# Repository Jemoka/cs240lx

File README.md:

## CS240lx Spr'26 (Y2E2-111 530pm)

This is a implementation-heavy, lab-based class.  We assume 140e as
a baseline and use this knowledge as a springboard to advance quickly
through a set of powerful, useful techniques that even many advanced
practioners don't know.

Like 140e you'll write custom code from scratch for the widely-used,
ARM-based raspberry pi; our code will run "bare-metal" without an
operating system, which means we can do interesting things without
constantly fighting with a lumbering OS that cannot get out of its
own way.

The course workload is significant, but we aim to not waste your
time. CS140E is strongly encouraged as a prerequisite, but a sufficiently
talented and motivated implementor can make up for its lack (as
calibration we usually have two or three people per year do this route).

### 240lx vs 140e 

Same rough format: 
  - still 2 days a week.
  - still hardware, low level code.
  - still pizza.

Contents:
  - Various cool tricks from 3+ decades of low level code.
  - Devices, speed, dynamic tools, code generation, OS tricks.  
    - Depends alot on what people are interested in.  
  - Probably at least one new board (pico, different riscv).

Differences:
  - usually stop around 10:30pm or so, vs 1:00am.
  - is more conceptual:
      - 140e must cover threads, interrupts, VM, FS, some network.
      - 240lx assumes you know that stuff, and use it to do
        other stuff.
  - class can replace cs240 (paper reading).
  - usually has the people who find 140e fun (+/-).
  - the final projects are wild.

Older versions:
  - [cs240lx-22](https://github.com/dddrrreee/cs240lx-22spr/tree/main/labs)
  - [cs240lx-23](https://github.com/dddrrreee/cs240lx-23spr/tree/main/labs)
  - [cs240lx-25](https://github.com/dddrrreee/cs240lx-25spr/tree/main/labs)

Alot of your favorite staff!
  - Head TA: Joseph Shetaye (rockets, booms, winning bets)
  - Maximilien Cura (Rust + insane hacks)
  - Aditya Sriram (ox64 riscv + bass)
  - Dawson Engler (sup)

---------------------------------------------------------------
### Class rules: no llm usage, no late labs.

This class is a brutal staff load.  140E last quarter:
 - Almost 2,000 checkoffs; 
 - Many (unpaid!) staff staying at lab from 530-midnight;
 - Everyone still has PTSD.

240lx has conceptually harder labs than 140e, much smaller staff, and
almost 2x last years enrollment.

So unfortunately we do have two draconian rules for survival.

*Rule 1: absolutely no labs accepted*:
  - You have 1 week to turn in each lab (earlier is better!).
  - We will not accept them after this.  
  - TAs can't deal with the load of late turn-ins.
  - Possible exceptions: you are presenting at a conference, 
    competing at a national championship, or doing a huge
    interesting extension.

*Rule 2: Absolutely no LLM usage for labs or extensions*:
  - You might not get caught, but if you do so we'll try to get you
    kicked out if you don't drop the class.
  - After the past year's experience, we've been forced into fascism.
  - The alternative is in-class blue book exams.  No one wants that.
  - If you want to use robots, *please* take the many other classes that
    are ok with it.  
  - There are much higher fidelity and much easier ways for us to see LLM
    output compared to the work and expense of this class.
  - WTS: we are developing "LLMs for low-level hardware" lab classes.  But
    they are intended as follow-on for those that understand how things
    work.

Sorry for the negative message. We live in interesting times. The path
ahead is unclear other than the neon glare of what has not worked well.

-----------------------------------------------------------------

### Possible labs

Always do: Generate executable code at runtime
  - even more low level than inline assembly.
  - self-modifying code is the ultimate sleazy hack.
  - used to make fast(er) interpreted languages (JIT for
    javascript, etc), fast dynamic intstrumentation (valgrind),
    and old school virtual machines (vmware).
  - can do all sorts of speed hacks by specializing using runtime
    information.  compiling data structures to code.  etc.

Always do: Custom pcb:
  - parthiv historically comes in to do a week of custom pcb labs so
    can make your own cool boards.

Always do: Build a bunch of tools using memory faults and single-stepping.
  - Eraser race detector 
  - Purify memory checker 
  - Advanced interleave checker.  
  - instruction level profiler measuring cycles, cache misses,
    etc.

Always do: Speed:
  - make low level operations (exceptions, fork/wait, pipe
    ping pong) 10-100x faster than laptop.  i think this is
    feasible but haven't done, so am interested.
  - overclocking the pi and seeing how fast can push it.
  - push the NRF using interrupts and concurrent tx, rx to 
    see how close can get to the hw limit.
  - make a digital analyzer (printk for electricity) where
    you get the error rate down to a small number of nanoseconds

And a few different communication protocols: 
  - how fast can send/recv data over gpio pins b/n two pis?
  - over IR
  - over speaker/mic.
  - over light and camera (?)
  - lora?

Device labs are fun.  So we do those too:
  - accelerometer, gyro
  - lidar
  - addressable light array
  - analog to digital converter.
  - lora so can send bytes 1km+

More systems-y device labs, by combining into
standalone tools:
  - acoustically reactive light display using mic, adc, 
    addressable light array.  extend to multiple systems.
  - little oscilliscope using oled display, mic, adc.

If we have more kernel hackers some subset of:
  - network bootloader
  - make an actual OS that ties all the stuff together.
  - small distributed system
  - distributed file system
  - actual clean fat32 r/w so can do distributed file system,
    firmware updates.
  - processes that migrate from one pi to another.
  - FUSE file system interface.

Big stuff missing from 140e:
  - makefiles
  - crazy C macro tricks.

Maybe other boards:
  - pico 2?  (slow, but small+cheap: has arm-m33 and risv)
  - ox64?  (risv)
  - if we do riscv: can write a simulator that will simulate itself
    on riscv in a couple of days.  can also make it symbolic.

Possible other stuf:
  - e.g., maybe some other languages (rust?  zig?)
  - static bug finder.

-----------------------------------------------------------------
### tl;dr:  getting setup.

  - get the class repo:

        git clone git@github.com:dddrrreee/cs240lx-26spr.git

  - define the `CS240LX_2026_PATH` environment variable to 
    point to where you put the class repo.  

        # for bash (in .bashrc or similar)
        export CS240LX_2026_PATH=<absolute path to your repo>

  - check that everything worked: plug in your pi, and run hello:

        % pwd
        /home/engler/class/cs240lx-26spr
        % cd labs/0-pi-setup
        % make

        ... alot of stuff ...
        listening on ttyusb=</dev/ttyUSB0>
        hello world from the pi
        DONE!!!
        
        Saw done

  - [look at the labs](./labs/README.md)
  - write code!

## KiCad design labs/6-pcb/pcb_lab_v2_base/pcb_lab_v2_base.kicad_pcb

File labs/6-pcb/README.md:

# PCB (KiCAD) Lab v2 by Parthiv

NOTE: KiCAD 10 was released last month (March 2026). I made this lab on KiCAD 9, but feel free to try KiCAD 10 and let me know if anything major has changed.

## Overview
This lab will be focused on designing printed circuit boards (PCBs), which many students in 140e/240lx/340lx have found useful over the years in final projects to help reduce wiring complexity and increase hardware reliability. The focus of the lab will be on how to replace a bundle of wires with an inexpensive PCB, and not on how to actually design electrical circuits (which is a much more complicated discussion). For the most part, you can get by just connecting breakout boards together. If you want to integrate a piece of hardware without a breakout board, most datasheets will include an "application circuit" that will show you what supporting hardware is needed.

Our goal is to create a board that can plug into the Raspberry Pi GPIO header and connect to a USB to UART converter along with some RGB LEDs. To extend the lab, you'll also add in connections to a few sensors/peripherals/hardware of your choice. 

## General Keyboard Shortcuts
I assume `Ctrl` becomes `Cmd` on mac.

* `Ctrl+S`: Save (do often!)
* `Ctrl+Z`: Undo
* `Ctrl+Y`: Redo

## Step 0: Prelab

Please review [PRELAB.md](./PRELAB.md). If interested, you can also check out a previous version of the lab [here](https://github.com/dddrrreee/cs240lx-23spr/tree/main/labs/16-pcb). In the original version of the lab, we focused on designing a board with NRF24L01 wireless transceivers. You can use that board for inspiration if you'd prefer to do something a little more "batteries included".

**A mouse will be very helpful!**

## Step 1: Creating a Project

1. Open up KiCAD (either type `kicad` in your terminal or search for it in your installed applications).
2. Go to File->New Project. Select a location where you want to create the project (you can do it in this directory) and give it a name. Ensure that the box to "Create a new folder for the project" is selected. Create the project.
3. You should see a window like this:

    On the left side, you can see a file called [project_name].kicad_pcb and another file called [project_name].kicad_sch. Double clicking these will open the PCB and Schematic editors respectively. We will learn what these are in more detail.

## Step 2: Creating a Schematic

1. In the main KiCAD window, double click the .kicad_sch file to open the Schematic editor. You'll probably get a popup saying that KiCAD is being run for the first time; just use the default option to "Copy default global symbol library table". Once that's done, you will see a blank schematic:

    The schematic is where we will describe what pins of what components connect to what other pins of other components. The analog here is your `.h` file. You'll definine the connections between components (like function interfaces) but not the actual physical implementation of those connections (like the function implementations in `.c`). You should try to keep this organized if you can! I will show you some strategies on how to do this. 

    You can middle click and drag to move, or scroll up/down to zoom. Ctrl+scroll will move you left/right and shift+scroll will move you up and down, if you prefer that to middle click and drag.

2. Go to Place->Add Symbol (or type the keyboard shortcut `A`). Again, if you get a popup here, "Copy default global footprint library". In the search bar, search for the symbol `Raspberry_Pi_2_3`. Select it, then click OK to start placing the component. Place it somewhere in the middle of the schematic by clicking. If you want to move it, you can click on it, hit `M`, and then move it around, then click again to place it. You'll immediately notice that the pins are laid out quite differently from the actual physical pins on the Pi. And you'll see just one GND, 5V, and 3.3V pin, though the Pi has many. This is one of the ways that we simplify the schematic view to make it a bit easier to see what's going on. In older versions of KiCAD, you may see all of the power pins represented; if so, you can just wire them all together in the schematic (see old version of the lab).

3. Now, we will connect the power rails of the Raspberry Pi. Hit `P` to open up the power symbol menu. Search for `GND`, select it, and hit OK to start placing the ground symbol. Put it near the bottom of the Raspberry Pi symbol. Hover over the end of one of the GND pins on the Pi, then hit `W` to start drawing a wire. Note that it'll start drawing a wire from wherever your mouse was; if it was in a bad spot, you can click `Esc` to cancel drawing the wire and try again. Connect the Pi's GND pin to the GND symbol you just placed.

    Next, add power symbols for `+5V` and `+3V3` to the schematic, and connect those to the 5V and 3V3 pins of the Pi.

4. Now that we've connected the power for the Pi, let's add the RGB LEDs. We are going to use the SK6812 LEDs, which are compatible with the more common WS2812 but work with the 3.3V logic level that the Pi outputs. Technically, WS2812 require 5V logic (though we often get away with 3.3V for small chains). You can review the SK6812 datasheet in [docs/SK6812.pdf](docs/SK6812.pdf). It's a pretty short datasheet and worth looking through the whole thing.

    In the schematic view, type `A` to add a new component, then search for `SK6812`. Place a few of them down (however many you'd like)! You can also just place one, click `Esc` to get out of the add component mode, then left click and drag to select the LED you placed, then Ctrl+C/Ctrl+V to duplicate it however many times. 
    
    Something to know is VDD (or sometimes VCC) in datasheets or component pinouts refers to the positive voltage, while VSS (or VEE) refers to ground.
    
    If you read the datasheet (read the datasheet!), you'll see that the manufacturer recommends placing capacitors between the 5V supply and ground near each of the LEDs. This is a pretty common thing you'll see to help provide a more stable voltage supply to more power-hungry components. Usually, they'll specify the capacitance properly (in pF, uF, or nF), but here you can see a 3-number code of `104`. A quick search will tell you that `104` is 100nF or 0.1uF. Let's add these capacitors too; the name in the parts menu is `C`.
    
    Go ahead and connect +5V and GND sources to each of the LEDs as required (type `P` to add power sources, `W` to draw wires). When drawing wires, if you click before reaching your destination, you'll get to decide where the wire turns in the schematic view which can be helpful for organization. It's common to just have a whole bunch of power sources all over the schematic to avoid drawing long wires between them. There is an implied connection between all sources with the same label. 

    Pro-tip: you can make one LED/capacitor/wires/sources unit and then copy/paste that a few times. 

    Apply the capacitance value to the capacitors by clicking on the capacitor, then typing `E` to edit. Then in the popup window, update the value in the `Value` field. This isn't enforced in any way, it's just a note so you know what it is when you're placing the capacitors on the PCB.

    Choose a Pi pin to connect the first LED's DIN port to. I chose GPIO12 (which is incidentally pin 32). Your schematic should look something like this:

5. Now, let's create a connector for a [USB/UART converter breakout board](https://www.amazon.com/MTDELE-CP2102-Serial-Adapter-Module/dp/B0D76NNWVW) so we can plug it directly into the PCB. Unfortunately, most breakout boards won't have an associated symbol in KiCAD, but it's good practice for creating new symbols. We'll want to create a symbol to represent the logical pins that the USB/UART has. Go to Tools->Symbol Editor. You will see a blank symbol editor like this:

    On the left, you can see various symbol libraries which contain different default parts that are common enough to be included in KiCAD. We will be creating a new one.

    In the symbol editor, go to File->New Library. If you make it Project, any parts you make will only be usable in the current project. If you make it Global, you can use it in future projects. I went with Project but either is ok. Give it whatever name you want (`cs340lx_pcb`, or something).

    On the left window, find the library you created and right click on it. Then click New Symbol, and you'll see a new window pop up. See below for recommended settings.

    Click on OK and create it. 

    ```
    If you can't find the library (seems to be happening on KiCAD 10), try the following workaround: 
    1. Go to `Preferences -> Manage Symbol Libraries` and then click `Project Specific Libraries`
    2. Delete the custom library if it's present.
    3. Re-add the library.
    ```

    On the left of the main window (to the right of the list of libraries), right click on the grid and select Edit Grids.

    In the window that shows up, change the Fast Grid Switching: Grid 1 to 100mil/2.54mm. This helps with alignment for placing pins in the symbol. Then close this window, and type `Alt+1` to switch to the 100mil/2.54mm grid. Make sure the bottom of the symbol editor shows `grid 100`.
    
    Now that setup is done, it's time to make the symbol. On the right side of the main window, select the Draw Rectangles tool and draw a rectangle on the screen. Don't worry, you can change it later. If you want to move the auto-generated text (`J`), you can click on it (press escape to reach select mode like in the schematic editor) and hit `M` to move it. Click to place.

    Now, we will add the pins. Hit `P` to create a pin. We'll make the `GND` pin, which is pin number 4 (4th from the top of the UART) and is a Power Output. The reason we choose Output is because the entire system's power/ground is going to be generated by the UART plugged into your computer.

    Place the pin down at the bottom of the rectangle, ensuring that the circle end of the pin is facing out (this is where you'll connect wires in the schematic). Click `R` to rotate the pin.

    Create the remaining 4 pins:

    - 1: 3V3, power output
    - 2: TX, output
    - 3: RX, input
    - 4: GND, power output (already did in step 11)
    - 5: 5V, power output

    Try to keep voltage at the top, ground at the bottom, and signals on the sides (like the Raspberry Pi symbol). You can grow and shrink the rectangle if needed by going to the select tool (escape) and then clicking on the border of the recctangle. Your symbol should look something like this (doesn't have to match exactly). You can rotate a pin with `R` and move with `M` like you'd expect.

    You can add text using the text tool on the right side. Once you've finished the UART symbol, save with Ctrl-S or Command-S, then exit the symbol editor. In the schematic editor, click `A` to add a symbol. Search for the UART you just created; you should see it pop up.

    Connect the 5V pin to your +5V rail, GND to GND, TX to the Pi RX and RX to the Pi TX. You can optionally connect 3V3 to +3V3, but this isn't strictly necessary since the Pi also creates its own 3V3 on the pins. I left it unconnected.

    By convention, if wires appear to cross but don't have a circle over the intersection, they are considered to NOT be connected.

    Hover over an unused pin on the Pi and hit `Q` to mark it as a No-Connect (looks like an X). This declares that you meant to not connect this pin and didn't just forget to connect it. Now, you're in no-connect placing mode and you can click on all the unused pins on the Pi/LEDs/UART/your custom hardware. Compare your schematic against the Completed Schematic section below, making sure that everything is connected the way it should be.

6. Create and add new symbols for your selected sensors of choice. If you used breakout boards, there should be very little/no additional supporting hardware and you should just be able to wire up to pins on the Pi. You can check datasheets or hookup guides to be sure. Feel free to ask Parthiv for help/confirmation. Make sure your pins are numbered correctly, which will make things much easier later on.

7. Annotate the schematic with `Tools->Annotate Schematic`. A window will pop up, click Annotate, which assigns reference designators (`C1`, `J2`, etc) to all the symbols. Click `Close`.

8. Now, go to `Inspect->Electrical Rules Checker` and click Run ERC to run the ERC. Make sure you annotate the schematic first; otherwise, you get a ton of weird errors. This is like a type checker in software; it will catch violations of electrical rules (type rules) but NOT correctness. And sometimes it rejects valid schematics (like a type checker can reject valid programs), which you will see.

    You will hopefully see 0-1 errors. If you connected the UART 3V3 to +3V3, you will not get the error I have. This error is because whoever made the Raspberry Pi Symbol decided to make the 3V3 pin a power input even though it's a power output. So the ERC thinks nobody is providing power to +3V3. We know this to be wrong (the Pi outputs 3V3) so we can ignore this.

    If you have other errors, address them and re-run ERC. A common error is forgetting to put a no-connect on a pin that is unconnected. Also, be careful with custom symbols that you properly assigned the pin types.

9. The last step is to assign footprints, which are the representation of each symbol in the real world PCB. Go to `Tools->Assign Footprints`, which will open a new window. 

    You will see that the LEDs have footprints already assigned. It's worthwhile to check the datasheet to make sure these are correct. We need to assign footprints for the other components. Click on the row with C1, then on the left side look for library `Capacitor_SMD` (capacitor, surface mount device). On the right side, look for footprint `Capacitor_SMD:C_0603_1608Metric`. This corresponds to a standard 0603 surface mount capacitor, which is a super common size. Double click on `Capacitor_SMD:C_0603_1608Metric`, which will assign that footprint to our capacitor.

    Go through and do this for all the components:

    - Both capacitors: `Capacitor_SMD:C_0603_1608Metric`
    - Pi: Library `Connector_PinSocket_2.54mm`, footprint `Connector_PinSocket_2.54mm:PinSocket_2x20_P2.54mm_Vertical` (0.1" female header, 2x20)
    - UART: Library `Connector_PinSocket_2.54mm`, footprint `Connector_PinSocket_2.54mm:PinSocket_1x05_P2.54mm_Horizontal` (0.1" female 90 degree header, 1x5).
    - Your selected breakout boards: probably a 2.54mm 1xN PinSocket for some N.

    Then click "Apply, Save Schematic & Continue". You can then close out of the Assign Footprints window and the schematic editor.

### Schematic Editor Keyboard Shortcuts

* `A`: add symbol
* `P`: add power symbol
* `Esc`: go to regular mouse (select) mode
* `M`: move (after selecting a symbol)
* `R`: rotate (after selecting a symbol)
* `E`: edit symbol properties (after selecting a symbol)
* `Q`: place no-connect symbol (should be in select mode first)
* `W`: draw wire (should be in select mode first)

### Schematic Editor Tools

* Tools->Symbol Editor: create new symbols
* Tools->Annotate Schematic: assign reference designators
* Tools->Assign Footprints: assign PCB footprints to schematic symbols
* Inspect->Electrical Rules Checker: validate against some rules

### Symbol Editor Keyboard Shortcuts

* `P`: add pin
* `Esc`: go to regular mouse (select) mode
* `M`: move (after selecting a symbol)
* `R`: rotate (after selecting a symbol)your Schematic 

## Step 2: Laying out the PCB

Time to create the PCB! For all of these steps, you don't have to match the exact thing I do. Actually better if you don't, so it's your board and not you making my board :D

1. From the KiCAD main window, double click the .kicad_pcb file to open the PCB editor. You will see a blank PCB, this time a black background instead of white (schematic).

    You can middle click and drag to move, or scroll up/down to zoom. Ctrl+scroll will move you left/right and shift+scroll will move you up and down, if you prefer that to middle click and drag.

2. Go to Tools->Update PCB From Schematic. This will open a window, click "Update PCB". You should do this any time you edit your schematic or assign new footprints in the schematic.

    Hopefully, there are zero warnings/errors. A common error is forgetting to assign a footprint to a symbol in the schematic. If you do this, then KiCAD is unsure what physical footprint to assign to the logical symbol you created in the schematic. Revisit step 19 from part 1 if this happens. Then, come back to the PCB viewer and this step again.

    If you have zero warnings/errors, then you can "Close" the window that popped up, and then click anywhere to place the mess of components.

    You will see a 2x20 pin header for the Pi, 1x5 header for the UART, LEDs, capacitors, and any additional headers/components for your chosen hardware.

    If you look at the picture at the very top of this page, you will see that the Pi header is on the underside of the board whereas everything else is on the top. To move the Pi connector to the backside of the board, click on it, then hit `F` to "flip" it to the back. You will see the outline change from pink to blue, and also the text related to the Pi header will be mirrored. 

    You can also go to View->3D viewer to see this, though there will probably be an error about not having a board outline yet (which we will fix shortly).

3. Now, we will try to organize the components reasonably well to minimize the length of the connections we need to make. Hit `Esc` to go to select mode, then click on any footprint. Once you've selected the footprint, you can rotate it with `R` or move it with `M`. Click to place when you're in move mode. 

    All of the thin lines you see connecting the different pins of components are connections we will eventually need to make, so trying to keep these as "untangled" as possible will make things easier. That being said, it's probably impossible to completely avoid crossing (it's not an issue to have crossing wires as we can route wires on the front and back of the board).

    I would recommend putting the Pi header at the top of the other components, with the +5V pads to the left. Then, put the UART near the left side of the Pi header (so there's a short path for +5V).

    Also, make sure to keep each capacitor close to the +5V pad of one of the LEDs. Technically, the way that our schematic is, we could connect them to anywhere on +5V and GND. However, we would like to keep the resistance on the path between the capacitor and the LED as small as possible, so that the capacitor can deliver power to the LED when it has current spikes when turned on bright. Here's one possible arrangement which is pretty reasonable:

    You'll see I assigned the wrong footprint for the UART (not a Horizontal/right angle header) so I went ahead and fixed that in the Schematic editor (Tools->Assign Footprints) then went back to the PCB editor and ran Tools->Update PCB from Schematic.

    If you're particular about alignment, you can select multiple components with Shift-Click and then right click. In the menu, select "Align/Distribute" and mess around till you get what you want. 

4. Now let's draw our board outlines. On the right side, you will see a bunch of Layers

    These each represent a different layer of the PCB. Some highlights:
    * `F` and `B` prefixes are for front and back, as we can have many things on either side of the board
    * `Cu`: front and back copper, which are where we make our connections. In a more-than-2 layer board, we will have `In1.Cu`, `In2.Cu`, etc.
    * `Adhesive`: some components are glued to the board, this layer shows where the glue should be placed
    * `Paste`: for surface-mount components, this is where the machine will automatically place solder paste. After components are automatically placed in their locations, the whole board is baked, melting the solder paste, then cooled, hardening the paste (and making electrical/mechanical connection with the components).
    * `Silkscreen`: text/drawings that are printed on the board for aesthetic/documentation reasons
    * `Mask`: The green (or other color) layer of the board which protects the underlying copper from corrosion and accidental shorts. It's expected that most of the board has mask, so the `Mask` layer is actually the negative. So it shows where there is _not_ mask.
    * `User.*`: these don't get printed, so you can put stuff for documentation
    * `Edge.Cuts`: the edges of the board which are cut.
    * `Courtyard`: bounding polygons for the various components. Ideally, no courtyards overlap so we can ensure that no components are inside each other. Just like we had an ERC in schematic, we have a DRC (design rules check) for the PCB which will complain if two courtyards overlap. However sometimes we know that we are safe (e.g. capacitor fits "under" NRF).

    You can enable/disable the visibility of layers by clicking the eye icon, which can be interesting. 

    You'll want to click on the `Edge.Cuts` layer and make sure the triangle is pointing to it (like in the image above). Select the rectangle tool (also selected in the image above). Now, draw a rectangle around the components you made by clicking once for one corner, then clicking again for the opposite corner. Give yourself some extra space for routing traces (wires) around the components. 

    Now, if you open View->3D Viewer, you will see your new outline.

    If you make it too big/too small, you can always edit this by clicking on the `Edge.Cuts` layer, then the select tool (`Esc`), then clicking on the corner of the rectangle and changing the shape. 

    You can also make a custom shape using a vector graphics tool like inkscape, then export as SVG. Then go to File->Import->Graphics and add your shape to the `Edge.Cuts` layer.

5. A common practice in PCB design is to make (almost) the entire front of the board be connected to your power rail, and (almost) the entire back of the board be connected to your ground rail (or vice versa). This helps you avoid having to manually connect every power and ground together, sort of like how we just connected them to the GND and +5V symbols on the schematic to avoid a ratsnest of wires between the power pins.

    We will do that now. Click on the `F.Cu` layer and do `Ctrl+Shift+Z` (mac: `Option+Z`) to open a window for "copper zone". Ensure that the `F.Cu` layer is selected on the left, then select the `+5V` net.

    Hit OK, then draw a rectangle that's bigger than the rectangle you drew for the edge cuts (this time, you need to click all 4 corners, not just 2 opposite). Repeat the process for `B.Cu` and `GND`. It should look something like this when you're done:

    If you mess up while you're drawing, you can hit `Esc` and try again.

6. Let's actually fill the zones to make the electrical connections. Hit `B` to fill zones. This should hopefully connect all of our +5V and GND connections for us! You'll see the connection lines for those disappear. If you zoom in to some pins, you will see what exactly happened:

    Notice that on the front side (red), where we made the 5V zone, KiCAD helpfully connected the pin with an X pattern. On the back side (blue), where we made the GND zone, KiCAD connected with an X pattern. It may be easier to see what's going on if you make one of the two copper layers invisible (see above). Make sure to turn it back on afterwards.

7. Now the fun begins: time to route our traces! Click on `F.Cu` on the left to route on the front of the board. Then, select a `1 mm` trace width. Move your mouse over the +5V pad on the UART (you can zoom with scroll wheel, and middle click+drag to pan). Hit `X` to enter trace mode. If you move your mouse, you will see a trace expanding out of the pad. 

    Each time you click in trace mode, you will "save" some of your progress that you've made. Once you reach your target, you can click on it to finish routing the trace. In general, try to avoid 90 degree turns. 

    Go ahead and connect the Pi pin you selected for the LED signal to the first LED. It's ok to go in between the pins of the Pi. Then, hit `B` to re-fill the zones, and you'll see a bit of the front +5V zone has been cleared out to allow the trace you just made to go through it. 

    Let's now route the other 2 UART connections. I started doing that, but it seems like my traces will have to cross!

    We have a few options on how to solve this. We can go all the way around with one of the connections.

    But you'll notice this cut off the Pi's +5V pins from the rest of the +5V zone, making an "island". KiCAD is drawing a short connection line between the main zone and the "island" to inform us of this. We could go ahead and connect this, but it's not ideal.

    We have two layers! We could, for example, just cross the signals by moving one to the back of the board. While routing one of the signals (with `X`), click `V` to enter Via mode, and then place the Via somewhere so you can swap sides of the board. Since the UART Module uses through-hole pins, it can connect directly on the backside to the backside trace. Surface mount components (like our LEDs and capacitors) can only connect on the side they're placed on, so you'd need another via to bring the signal back to the front.

    We can also just route the whole signal on the back of the board. If you're not currently routing any trace (`Esc`), then clicking `V` will swap you between the front and the back. If you're on the back, the board will appear blue. 

    This is a bit of a contrived/silly example, but hopefully it demonstrates that you have a lot of options available when routing more complicated netlists. You may have to experiment with different solutions to problems and backtrack if things get too complicated. An absolute worst case scenario is to go a 4-layer board. It just increases cost (though not by a lot if you are ok with all your vias going all the way through the board). Most projects you'd do should be routable on 2 layers.

8. Finish up routing the surface mount components. You'll notice that the GND pins on the LEDs and capacitors cannot connect to the GND plane on the back; this is because they are surface mount components and only connect to the front by default. Add vias for those, either by starting a routing with `X` and then hitting `V` to place a via, or by hitting `Ctrl+Shift+X` to place a via directly. After placing the via and selecting the GND net, you can then route.
    
    Finish up routing your custom hardware, then save (hopefully you've been doing this throughout). You can admire your work in the View->3D Viewer!

9. I would recommend adding some annotations on the Silkscreen. You can click the `F.Silkscreen` (or `B.Silkscreen`) on the right side, then the text tool, and add annotations. At the very least, it's good to write the pin names on the various connectors (or at least enough that you plug it in the right way). And label the different connectors if you have several.

    My completed base PCB:

10. Almost done with the board! Let's run DRC (design rules checker) which will make sure our board is manufacturable. Go to Inspect->Design Rules Checker. In the window that pops up, enable "Test for parity between PCB and schematic" just to be sure.

Click Run DRC. If you have errors, go to the DRC Errors section below for common errors. For each, I'd recommend you zoom in super close, then click the entry in the DRC window. You will see an arrow in the middle of your screen. Address the issue and then click Run DRC in the window again. If there are other errors, ask me and I can help you out. 

If you get an error about the two +3V3 pads not being connected, this is because we don't actually use those for anything. If you'd like, you can disconnect the +3V3 in your schematic, mark it not-connected, and then return to the PCB and Update PCB from Schematic. Then, the connection requirement should disappear and DRC will be clean.

### Routing Tips

#### Clearance
Try to give clearance to pads and don't route traces too close to them (especially ones that connect to planes). This makes it easier in the future to route signals from those pads.

#### Try, try, try again

Don't be afraid to delete an old trace and re-route it if you find you need to move it to make something else work.

#### Zone Islands
An extremely common issue that people ran into was creating a filled zone "island", like below: 

Notice how the two traces have created an almost closed-loop, which cuts off a section of the filled zone into an island that's disconnected from the rest. An easy fix is to open the closed loop by moving one or more of the segments of the traces onto the other layer. If you go to the select mode (`Esc`), then click on a piece of trace, then hit `E`, then swap the layer to the other layer. You can then go and place vias (`Ctrl+Shift+V`, or `Opt+V` for mac?) on each end of the segment that you flipped to the other side to make electrical connection.

Another (worse) solution is to to put a via on the island and off the island and route a "jump" on the other side of the board. This isn't really recommended though, since it means there is higher resistance on the power plane (vias introduce resistance).

### DRC Errors

Here are some common DRC errors/warnings

#### Track has unconnected end

You have some track that is only connected on one side and can just be deleted. A tricky one is when the track is contained entirely inside a pad hole, so it's invisible (see below). Just click on the exact tip of the arrow that is pointing out the error and it should get highlighted. Then just hit `Del`. It helps to be VERY zoomed in on the PCB editor window.

#### Silkscreen clipped by solder mask

You have silkscreen that is either drawn off the edge of the board, or overlaps a pad somehow. Either expand your board (go to `Edge.Cuts` layer, then `Esc` to select, then click and expand the rectangle). Or move the silkscreen item (go to appropriate `*.Silkscreen` layer, then `Esc` to select, then click item, then `M` to move it). Below you can see I drew my board too small so the silkscreen hangs off the edge.

### PCB Editor Keyboard Shortcuts
* `Esc`: go to regular mouse (select) mode
* `M`: move (after selecting a footprint)
* `R`: rotate (after selecting a footprint)
* `F`: flip footprint (after selecting a footprint)
* `Ctrl+Shift+Z` (or `Opt+Z` on Mac?): create filled zone
* `B`: fill zones
* `X`: route trace
* `V`: swap active copper layer (front to back or vice versa)
* `Ctrl+Shift+V` (or `Opt+V` on Mac?): create via
* `E`: edit properties
* `Ctrl+Shift+T` (or `Opt+T` on Mac?): add text (in silkscreen layer)

### PCB Editor Tools
* Tools->Update PCB From Schematic: Apply any updates from the schematic editor (make sure to save in schematic editor)
* View-3D Viewer: view a 3D model of your board
* Inspect->Design Rules Checker: validate that it's manufacturable

## Step 3: Manufacture the PCB

The steps below are for JLCPCB, which is a PCB fabrication/assembly company in China that I've used for many years. Their prices are hard to beat, though there are many other companies that offer similar services (e.g. PCBWay). Feel free to addapt this to another vendor if you see something promising, I'd love to hear what your experience is. 

With JLCPCB, you can just fabricate PCBs (i.e. print the boards without any components attached), but you can also have them assemble the boards (solder some/all of the parts to the board). When dealing with small surface-mount parts, or large quantities of PCBs, it can be worthwhile to have them assemble the boards for you. You can view their full library of parts [here](https://jlcpcb.com/parts). If you see any references to "LCSC", this was what JLCPCB parts used to be called a few years ago.

### Install KiCAD JLCPCB Tools

This extension will make it a lot simpler to generate the files that JLCPCB needs.

Follow the instructions [here](https://github.com/Bouni/kicad-jlcpcb-tools?tab=readme-ov-file#installation-) to install `kicad-jlcpcb-tools`. Reproduced:

1. From the main KiCAD window, visit `Tools` -> `Plugin and Content Manager`
2. Click `Manage` next to the dropdown (which is likely pre-populated with `KiCad official repository`.
3. In the window that pops up, add `Bouni's KiCad repository` at 
    ```
    https://raw.githubusercontent.com/Bouni/bouni-kicad-repository/main/repository.json
    ```

4. Hit Save.
5. Select Bouni's KiCad repository in the dropdown, then select `KiCAD JLCPCB tools` and Install it.
    
6. Click `Apply Pending Changes` in the bottom right corner. This should install the extension.
7. Close out of the Plugin and Content Manager.

### The Goal 
 
We will be producing files for both fabrication and assembly.
* For fabrication, we create a set of Gerber files. Gerber is an ASCII vector format that is used to describe each layer of the board. For example, `F.Cu` gets its own Gerber file, as does `B.Silkscreen`. At this point, the board layout we've done already contains all the info needed to produce these.
* For assembly, we create a CPL (Component Placement List) file, which is just a CSV describing the position and rotation of each component. This is indexed by identifier (e.g. `C1` or `J2`). KiCAD already has the info needed for this. We also need a BOM (Bill of Materials) file, which is a CSV describing what JLCPCB part number should be placed for each component. This is also indexed by identifier. This is the thing that's missing which we need to assign here. 

### Assigning JLCPCB Part Numbers

Now, we'll assign part numbers for JCLPCB assembly.

1. Go to the PCB editor, then open `Tools -> External Plugins -> JLCPCB Tools`.
2. It will take a few seconds to download JLCPCB's part library. Afterwards, you should see a window like this, with a list of identifiers and currently empty columns with the LCSC (JLCPCB parts) info.

3. For each part, search the [JLCPCB parts site](https://jlcpcb.com/parts) using the description of your part and the footprint. **It is imperative that you verify that the footprint matches.** Particularly for more complex parts (integrated circuits, sensors, RGB LEDs, etc.), things can come with multiple footprints and pin layouts. You can always create a new footprint using the `Footprint Editor` (left as an exercise to the reader) if needed. I selected this RGB LED by searching `SK6812 PLCC4` which is the name of the LED (`SK6812`) and the footprint type (`PLLC4`) as seen in the list of parts in the JLCPCB tools window.

4. Copy the JLCPCB part number (e.g. `C5378720`) to your clipboard.

4. Click the identifier you want to apply the part number to. Ensure `Auto-select Alike` is enabled on the right so other idenfiers with the same footprint and value should also get selected. Right click, then `Paste LCSC`.

5. Repeat 3/4/5 until all your parts are assigned. Some that I found on a cursory look:

    | Description | JLC Part # |
    |-------------|------------|
    | 2x20 header | C2977589   |
    | 1x5 header  | C50950     |
    | RGB LED     | C5378720   |
    | 100nF cap   | C1590      |

    It's better to find "Basic" parts when possible (not "Extended") as they cost less to assemble. This is because Basic parts are kept in stock closer to the pick and place machines, I think. For the most part, it's just standard surface mount capacitors/resistors that are Basic. If you're doing something more custom, feel free to ask me if you have questions. Here's what mine looked like when done. 

6. Click `Save Mappings` on the right.

### Generate Production Files

We're now ready to generate the production files for JLCPCB!

1. Going back to your PCB view, select a silkscreen layer and add some text (shortcut: `Ctrl+Shift+T`). The text should say `JLCJLCJLCJLC`; this will get replaced by JLCPCB with the serial number of your order. I like to put it on the back, out of the way of anything else.

2. Back in the JLCPCB tools window, click `Generate` in the top left. It will run DRC for you, and you may get an error about `--refill-zones` not working. If that happens, ensure you refill zones (`B` in the PCB editor) and run DRC, then go to the JLCPCB tools `Settings` and disable the option to `Force DRC check before Gerber export`. 

3. You should see a log about where the gerber files were generated. It's good practice to go to KiCAD's main window, open the `Gerber Viewer`, and then go to `File -> Open Gerber Plot File(s)`, and navigate to/select all the `gbr` files in the generated `jlcpcb/gerber` directory. Ensure that things look reasonable, you can click through the various layers on the right side.

### Upload to JLCPCB

Now, let's go through JLCPCB to set up the manufacturing run. It's good practice to do this, even if you won't ultimately order. 

1. Visit the [JLCPCB quote page](jlcpcb.com/quote) and click `Add Gerber File`. Navigate to your JLCPCB project, and find the `jlcpcb/production_files` directory. In there, you'll find a zip of your gerbers which you can upload directly. 

2. You can leave most of the fabrication options as the default, but feel free to choose a new PCB color (or change any of the other knobs) if you'd like. 

3. On the `Mark on PCB` option, set this to `Order Number(Specify Position)`. This'll put your order number wherever the `JLCJLCJLCJLC` text from earlier was.

4. Set up assembly. Note that if you're doing assembly, you can upgrade to 24 hour fabrication for free on the right side. If you just need parts on one side, then Economic works. Otherwise you'll need Standard. A reasonable compromise could be to assemble all your surface mount parts on one side using Economic, and then solder your backside through-hole parts (generally just the 2x20 for raspi) by hand. When I make 150 boards for 140e, I just have them do the full thing, though.

You can select `PCBA Qty` to be less than the number of boards you're fabricating. I enable `Confirm Parts Placement` (they email you a final render of the parts placement) but leave everything else default usually. 

5. Hit `Next` and sign in / create account. Hit `Next` until you reach the `Bill of Materials` page.

6. Upload the BOM and CPL files from your `jlcpcb/production_files` generated directory. Hit `Process BOM & CPL`. 

7. You should see a processed BOM linking to the various JLCPCB parts. If you have chosen something with insufficient stock, it should tell you here and allow you to reassign.

8. Hit `Next` to get to the `Component Placements`. You'll see a 3D viewer like we had in KiCAD. The vast majority of the time, parts will be rotated wrong. Note here that the UART header is rotated 90 degrees, but on top of that, the LEDs are also rotated 180 degrees. The latter one is more subtle. You can tell because there's a "notch" in the silkscreen for pin 1, and this doesn't align with the "arrow" in the 3D model for pin 1. In general, that's your best bet for confirming part rotation for integrated circuits like this. 

You'll also see that for this model, the VDD pin is specified and I can cross-reference with the KiCAD PCB design.

For simpler polarity-sensitive components (electrolytic capacitors, single-color LEDs, diodes, etc.), JLCPCB generally shows a pretty obvious `+` on the positive side.

9. Right click on the incorrect parts one-by-one, and rotate them the appropriate amount to correct. 

10. Hit `Next`, and you should get your quote and be able to `Save to Cart`! Congrats!

## Step 4: Extensions

Here are some ideas for extensions.

1. Rather than using a CP2102 breakout board, look up a datasheet and place your own CP2102 chip and all of the various supporting components so you can plug a USB cable into your PCB and talk UART with your Pi. You can also check out the included `parthiv_pcb_v2.1` project which will contain a sub-schematic for the CP2102N and supporting hardware. You can copy this schematic into your project and import it, though it's a good exercise to build it from a datasheet. 

2. You can also do the same with any raw part that you selected, which will often be much cheaper than doing it with the breakout for volume production. However, I would always suggest having the breakout board as a backup option to help you determine if bugs are software-related or hardware-related. Check out JLCPCB parts to see what's available for manufacturing.

3. Create some interesting artwork and integrate it into the board shape, silkscreen, and/or component layout of your board.

4. Use the [KiCAD python API](https://gitlab.com/kicad/code/kicad-python) to programatically define aspects of your layout. For example, you can place a bunch of LEDs into a grid.

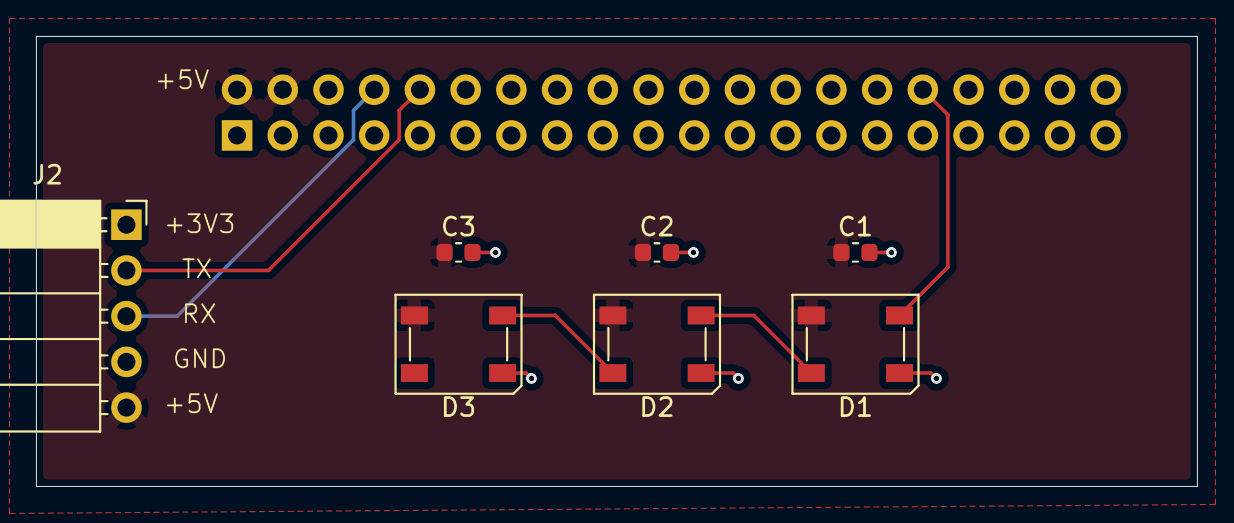
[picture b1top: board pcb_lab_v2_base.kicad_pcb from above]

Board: 2 copper layers, 64.5 x 25.0 mm, 8 parts (1 on the bottom side), 7 nets.

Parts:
C1, C2, C3: 100nF; C_0603_1608Metric
D1, D2, D3: SK6812; LED_SK6812_PLCC4_5.0x5.0mm_P3.2mm
J1: Raspberry_Pi_2_3; PinSocket_2x20_P2.54mm_Vertical
J2: UART; PinSocket_1x05_P2.54mm_Horizontal

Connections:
+5V: C1.1, C2.1, C3.1, D1.3 (VDD), D2.3 (VDD), D3.3 (VDD), J1.2 (5V), J1.4 (5V), J2.5 (+5V)
GND: C1.2, C2.2, C3.2, D1.1 (VSS), D2.1 (VSS), D3.1 (VSS), J1.6 (GND), J1.9 (GND), J1.14 (GND), J1.20 (GND), J1.25 (GND), J1.30 (GND), J1.34 (GND), J1.39 (GND), J2.4 (GND)
unnamed: D1.2 (DIN), J1.32 (PWM0/GPIO12)
unnamed: D1.4 (DOUT), D2.2 (DIN)
unnamed: D2.4 (DOUT), D3.2 (DIN)
unnamed: J1.8 (GPIO14/TXD), J2.3 (RX)
unnamed: J1.10 (GPIO15/RXD), J2.2 (TX)

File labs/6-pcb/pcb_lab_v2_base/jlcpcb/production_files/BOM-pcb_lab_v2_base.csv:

Comment,Designator,Footprint,LCSC,Quantity
100nF,"C1,C2,C3",C_0603_1608Metric,C1590,3
Raspberry_Pi_2_3,J1,PinSocket_2x20_P2.54mm_Vertical,C2977589,1
SK6812,"D1,D2,D3",LED_SK6812_PLCC4_5.0x5.0mm_P3.2mm,C5378720,3
UART,J2,PinSocket_1x05_P2.54mm_Horizontal,C50950,1

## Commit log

2026-03-31 minor
2026-04-06 fixed
2026-04-08 two labs
2026-04-09 new lab
2026-04-10 vector base
2026-04-14 parthiv lab
2026-04-15 daniel model gc
2026-04-22 added libmi
2026-05-12 memtrace
2026-05-13 that's where the fuck my redzone went
2026-05-13 dmode
2026-05-15 drivers mm
2026-05-21 added
2026-05-22 Revert "minor"
    This reverts commit 50f2ea8aa70c24cf333cdee9c42c041327c69ed4.
2026-05-22 Revert "Revert "minor""
    This reverts commit f0bccf6ec1f6b986a8ff183475246628836af9e6.
2026-05-27 nice
2026-05-29 eraser
2026-05-30 some more dma thinsg
2026-05-31 lmao
